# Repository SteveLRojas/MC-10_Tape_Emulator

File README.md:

# MC-10_Tape_Emulator
Unified HW and SW repository for the TRS-80 MC-10 tape emulator project.

## Dev Plan (USB Lib/FATFS)
✅- Get the STM to compile, 
- investigate funcs on top of in/out/transact to see how to use them to accomplish various operations
- Try to enumerate?
- Build bulk-only stuff?
- Implement SCSI stuff using bulk-only?
- ...??
- Glue functions?

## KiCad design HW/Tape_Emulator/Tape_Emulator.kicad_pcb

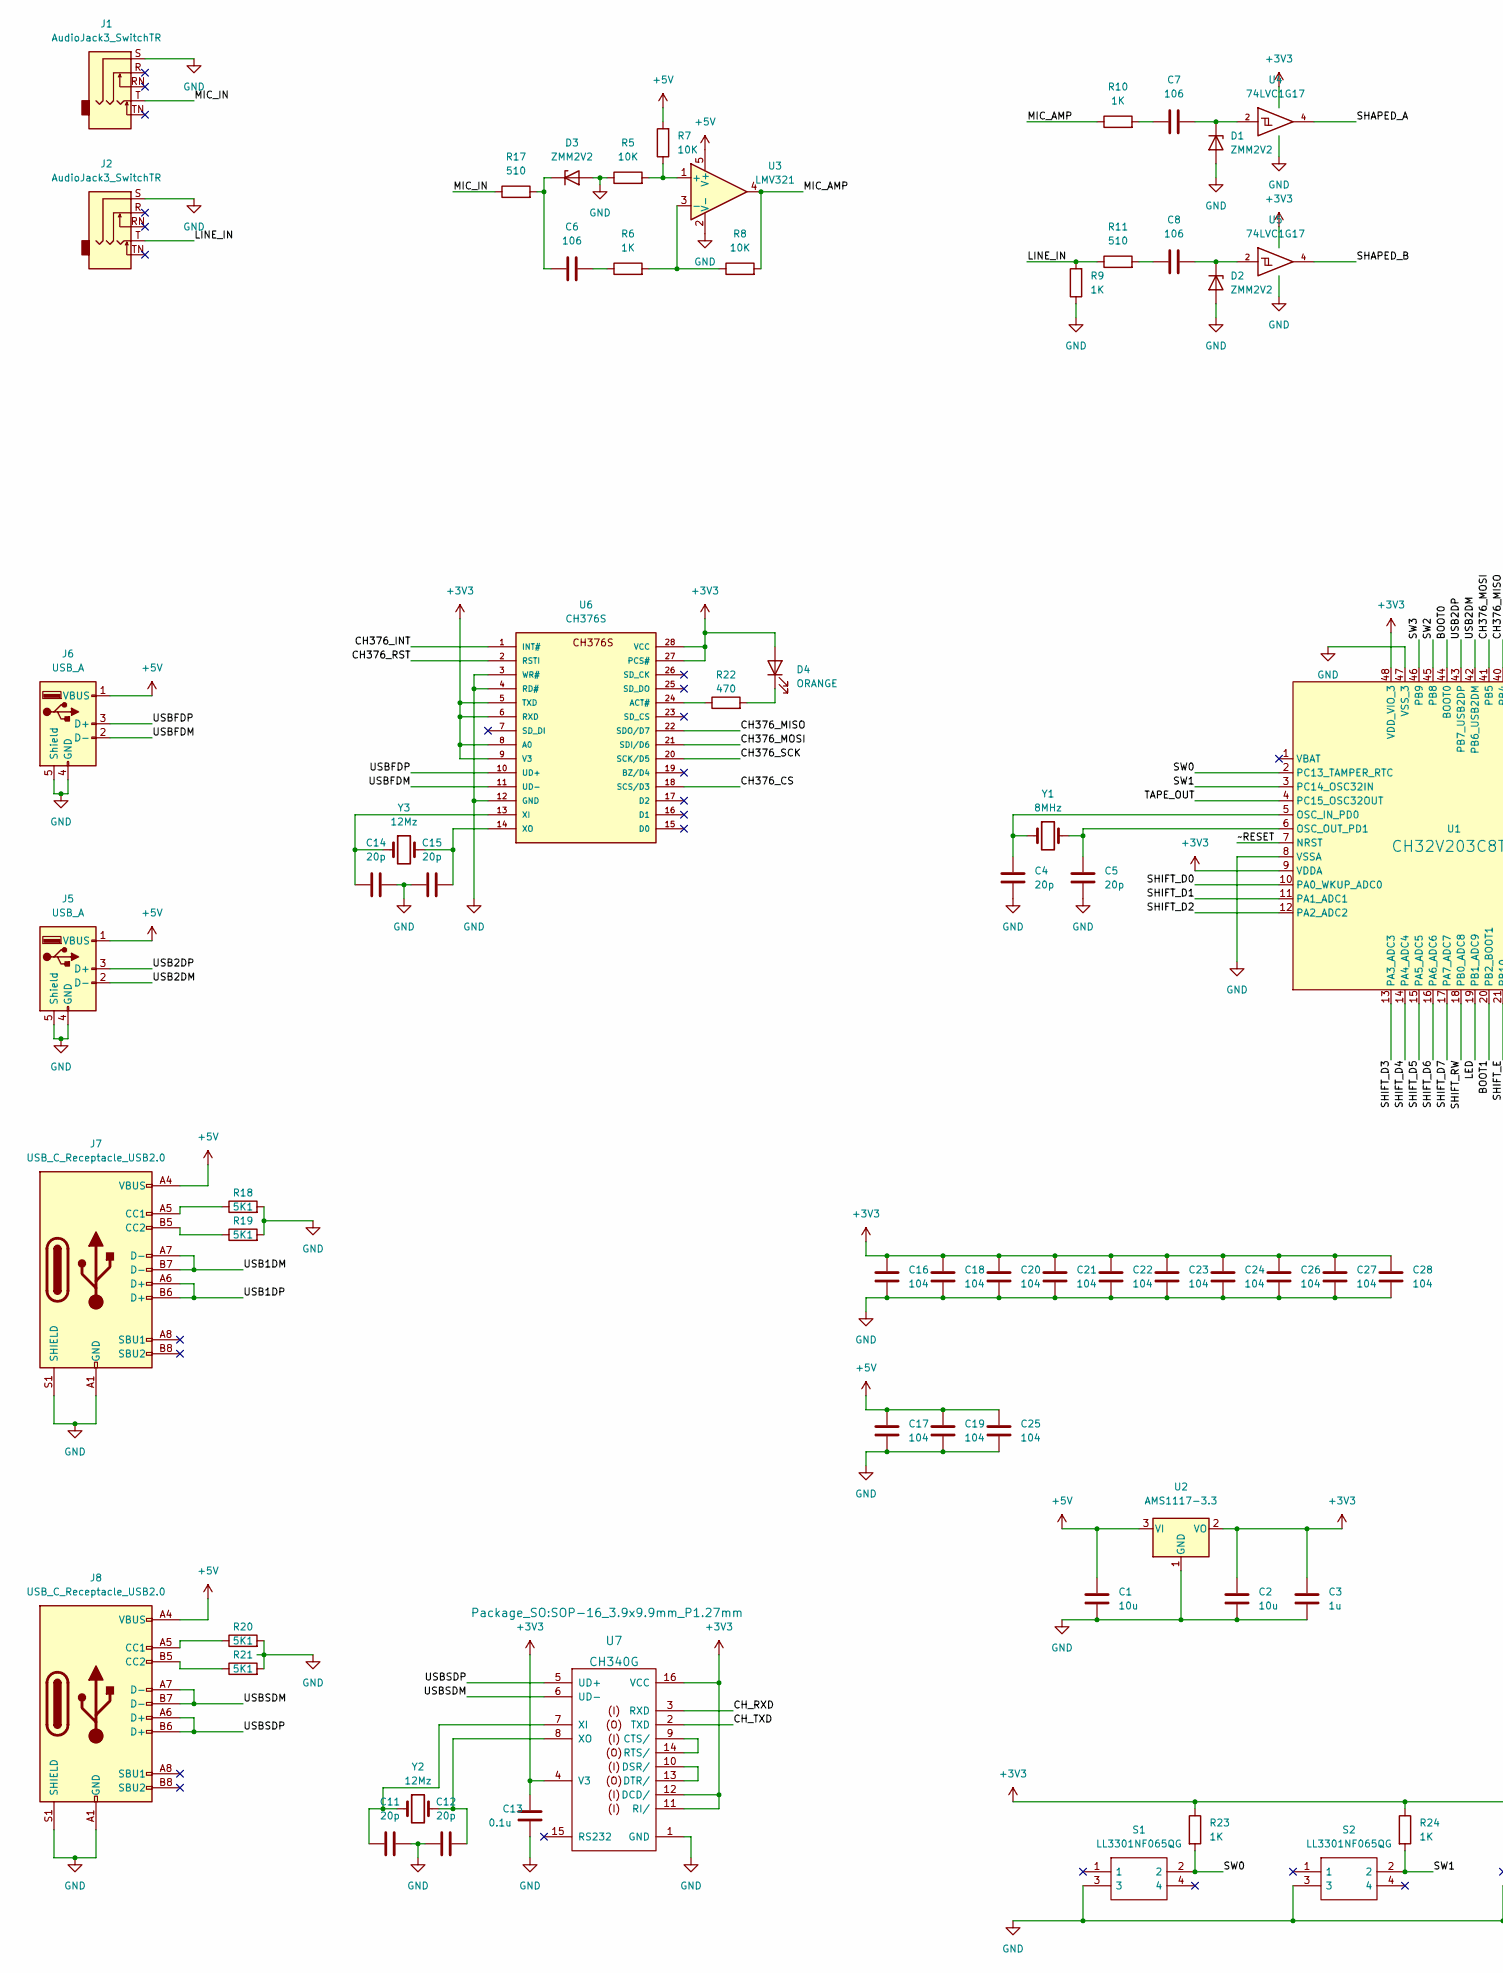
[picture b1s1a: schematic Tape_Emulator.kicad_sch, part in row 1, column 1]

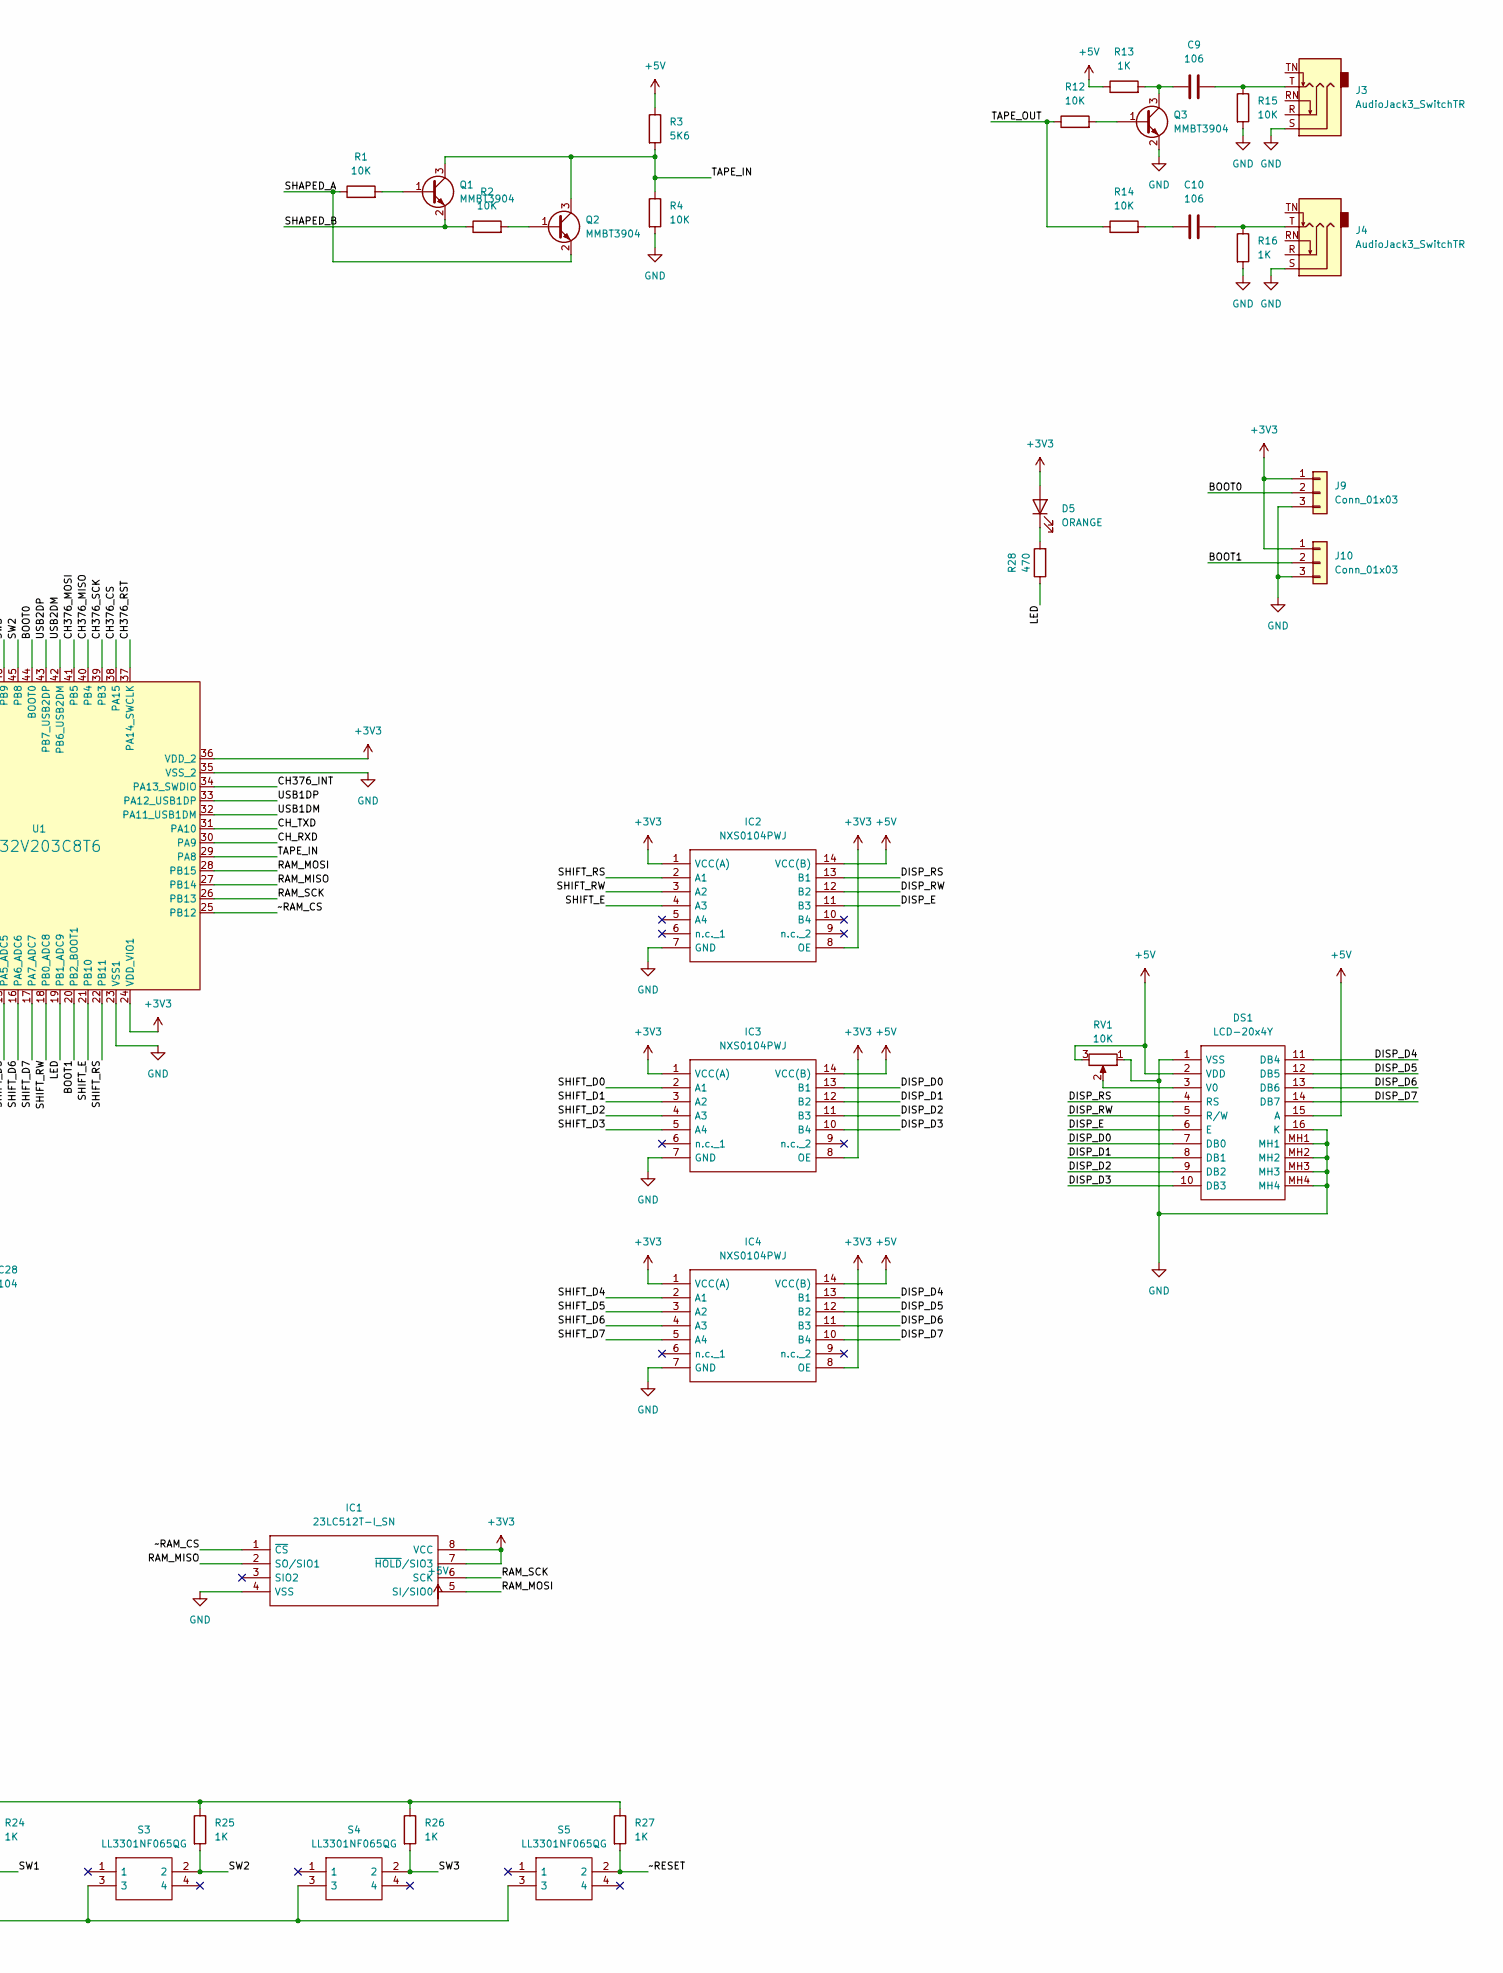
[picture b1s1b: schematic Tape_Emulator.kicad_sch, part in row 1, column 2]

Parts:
C1, C2: 10u; C_1206_3216Metric
C3: 1u; C_0805_2012Metric
C4, C5, C11, C12, C14, C15: 20p; C_0805_2012Metric
C6, C7, C8, C9, C10: 106; C_1206_3216Metric
C13: 0.1u; C_0805_2012Metric
C16, C17, C18, C19, C20, C21, C22, C23, C24, C25, C26, C27, C28: 104; C_0805_2012Metric
D1, D2, D3: ZMM2V2; D_MiniMELF
D4, D5: ORANGE; LED_0805_2012Metric
DS1: LCD-20x4Y; LCD20x4Y; Mouser Part Number 992-LCD-20X4Y
IC1: 23LC512T-I_SN; SOIC127P600X175-8N; Mouser Part Number 579-23LC512T-I/SN
IC2, IC3, IC4: NXS0104PWJ; SOP65P640X110-14N; Mouser Part Number 771-NXS0104PWJ
J1, J2, J3, J4: AudioJack3_SwitchTR; Jack_3.5mm_CUI_SJ1-3525N_Horizontal
J5, J6: USB_A; USB_A_CONNFLY_DS1095-WNR0
J7, J8: USB_C_Receptacle_USB2.0; USB_C_Receptacle_HRO_TYPE-C-31-M-12
J9, J10: Conn_01x03; PinHeader_1x03_P2.54mm_Vertical
Q1, Q2, Q3: MMBT3904; SOT-23
R1, R2, R4, R5, R7, R8, R12, R14, R15: 10K; R_0805_2012Metric
R3: 5K6; R_0805_2012Metric
R6, R9, R10, R13, R16, R23, R24, R25, R26, R27: 1K; R_0805_2012Metric
R11, R17: 510; R_0805_2012Metric
R18, R19, R20, R21: 5K1; R_0805_2012Metric
R22, R28: 470; R_0805_2012Metric
RV1: 10K; Potentiometer_Runtron_RM-065_Vertical
S1, S2, S3, S4, S5: LL3301NF065QG; Mouser Part Number 612-LL3301NF065QG
U1: CH32V203C8T6; CH32V203C8T6_LQFP-48_7x7mm_P0.5mm
U2: AMS1117-3.3; SOT-223-3_TabPin2
U3: LMV321; SOT-23-5
U4, U5: 74LVC1G17; SOT-23-5
U6: CH376S; SOP28
U7: CH340G; SOP-16_3.9x9.9mm_P1.27mm
Y1: 8MHz; Crystal_HC49-4H_Vertical
Y2, Y3: 12Mz; Crystal_HC49-U_Vertical

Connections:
+3V3: C2.1, C3.1, C13.1, C16.1, C18.1, C20.1, C21.1, C22.1, C23.1, C24.1, C26.1, C27.1, C28.1, D4.2 (A), D5.2 (A), IC1.7 (~HOLD/SIO3), IC1.8 (VCC), IC2.1 (VCC(A)), IC2.8 (OE), IC3.1 (VCC(A)), IC3.8 (OE), IC4.1 (VCC(A)), IC4.8 (OE), J9.1, J10.1, R23.1, R24.1, R25.1, R26.1, R27.1, U1.9 (VDDA), U1.24 (VDD_VIO1), U1.36 (VDD_2), U1.48 (VDD_VIO_3), U2.2 (VO), U4.5 (VCC), U5.5 (VCC), U6.5 (TXD), U6.6 (RXD), U6.8 (A0), U6.9 (V3), U6.27 (PCS#), U6.28 (VCC), U7.4 (V3), U7.11 (RI/), U7.12 (DCD/), U7.16 (VCC)
+5V: C1.1, C17.1, C19.1, C25.1, DS1.2 (VDD), DS1.15 (A), IC2.14 (VCC(B)), IC3.14 (VCC(B)), IC4.14 (VCC(B)), J5.1 (VBUS), J6.1 (VBUS), J7.A4 (VBUS), J7.A9 (VBUS), J7.B4 (VBUS), J7.B9 (VBUS), J8.A4 (VBUS), J8.A9 (VBUS), J8.B4 (VBUS), J8.B9 (VBUS), R3.1, R7.2, R13.1, RV1.3, U2.3 (VI), U3.5 (V+)
/BOOT0: J9.2, U1.44 (BOOT0)
/BOOT1: J10.2, U1.20 (PB2_BOOT1)
/CH376_CS: U1.38 (PA15), U6.18 (SCS/D3)
/CH376_INT: U1.34 (PA13_SWDIO), U6.1 (INT#)
/CH376_MISO: U1.40 (PB4), U6.22 (SDO/D7)
/CH376_MOSI: U1.41 (PB5), U6.21 (SDI/D6)
/CH376_RST: U1.37 (PA14_SWCLK), U6.2 (RSTI)
/CH376_SCK: U1.39 (PB3), U6.20 (SCK/D5)
/CH_RXD: U1.30 (PA9), U7.3 (RXD)
/CH_TXD: U1.31 (PA10), U7.2 (TXD)
/DISP_D0: DS1.7 (DB0), IC3.13 (B1)
/DISP_D1: DS1.8 (DB1), IC3.12 (B2)
/DISP_D2: DS1.9 (DB2), IC3.11 (B3)
/DISP_D3: DS1.10 (DB3), IC3.10 (B4)
/DISP_D4: DS1.11 (DB4), IC4.13 (B1)
/DISP_D5: DS1.12 (DB5), IC4.12 (B2)
/DISP_D6: DS1.13 (DB6), IC4.11 (B3)
/DISP_D7: DS1.14 (DB7), IC4.10 (B4)
/DISP_E: DS1.6 (E), IC2.11 (B3)
/DISP_RS: DS1.4 (RS), IC2.13 (B1)
/DISP_RW: DS1.5 (R/W), IC2.12 (B2)
/LED: R28.1, U1.19 (PB1_ADC9)
/LINE_IN: J2.T, R9.2, R11.1
/MIC_AMP: R8.2, R10.1, U3.4
/MIC_IN: J1.T, R17.1
/RAM_MISO: IC1.2 (SO/SIO1), U1.27 (PB14)
/RAM_MOSI: IC1.5 (SI/SIO0), U1.28 (PB15)
/RAM_SCK: IC1.6 (SCK), U1.26 (PB13)
/SHAPED_A: Q2.2 (E), R1.1, U4.4
/SHAPED_B: Q1.2 (E), R2.1, U5.4
/SHIFT_D0: IC3.2 (A1), U1.10 (PA0_WKUP_ADC0)
/SHIFT_D1: IC3.3 (A2), U1.11 (PA1_ADC1)
/SHIFT_D2: IC3.4 (A3), U1.12 (PA2_ADC2)
/SHIFT_D3: IC3.5 (A4), U1.13 (PA3_ADC3)
/SHIFT_D4: IC4.2 (A1), U1.14 (PA4_ADC4)
/SHIFT_D5: IC4.3 (A2), U1.15 (PA5_ADC5)
/SHIFT_D6: IC4.4 (A3), U1.16 (PA6_ADC6)
/SHIFT_D7: IC4.5 (A4), U1.17 (PA7_ADC7)
/SHIFT_E: IC2.4 (A3), U1.21 (PB10)
/SHIFT_RS: IC2.2 (A1), U1.22 (PB11)
/SHIFT_RW: IC2.3 (A2), U1.18 (PB0_ADC8)
/SW0: R23.2, S1.2, U1.2 (PC13_TAMPER_RTC)
/SW1: R24.2, S2.2, U1.3 (PC14_OSC32IN)
/SW2: R25.2, S3.2, U1.45 (PB8)
/SW3: R26.2, S4.2, U1.46 (PB9)
/TAPE_IN: Q1.3 (C), Q2.3 (C), R3.2, R4.1, U1.29 (PA8)
/TAPE_OUT: R12.1, R14.1, U1.4 (PC15_OSC32OUT)
/USB1DM: J7.A7 (D-), J7.B7 (D-), U1.32 (PA11_USB1DM)
/USB1DP: J7.A6 (D+), J7.B6 (D+), U1.33 (PA12_USB1DP)
/USB2DM: J5.2 (D-), U1.42 (PB6_USB2DM)
/USB2DP: J5.3 (D+), U1.43 (PB7_USB2DP)
/USBFDM: J6.2 (D-), U6.11 (UD-)
/USBFDP: J6.3 (D+), U6.10 (UD+)
/USBSDM: J8.A7 (D-), J8.B7 (D-), U7.6 (UD-)
/USBSDP: J8.A6 (D+), J8.B6 (D+), U7.5 (UD+)
/~RAM_CS: IC1.1 (~CS), U1.25 (PB12)
/~RESET: R27.2, S5.2, U1.7 (NRST)
GND: C1.2, C2.2, C3.2, C4.2, C5.2, C11.2, C12.1, C13.2, C14.2, C15.1, C16.2, C17.2, C18.2, C19.2, C20.2, C21.2, C22.2, C23.2, C24.2, C25.2, C26.2, C27.2, C28.2, D1.2 (A), D2.2 (A), D3.2 (A), DS1.1 (VSS), DS1.16 (K), DS1.MH1, DS1.MH2, DS1.MH3, DS1.MH4, IC1.4 (VSS), IC2.7 (GND), IC3.7 (GND), IC4.7 (GND), J1.S, J2.S, J3.S, J4.S, J5.4 (GND), J5.5 (Shield), J6.4 (GND), J6.5 (Shield), J7.A1 (GND), J7.A12 (GND), J7.B1 (GND), J7.B12 (GND), J7.S1 (SHIELD), J8.A1 (GND), J8.A12 (GND), J8.B1 (GND), J8.B12 (GND), J8.S1 (SHIELD), J9.3, J10.3, Q3.2 (E), R4.2, R5.1, R9.1, R15.2, R16.2, R18.2, R19.2, R20.2, R21.2, RV1.1, S1.3, S2.3, S3.3, S4.3, S5.3, U1.8 (VSSA), U1.23 (VSS1), U1.35 (VSS_2), U1.47 (VSS_3), U2.1 (GND), U3.2 (V-), U4.3 (GND), U5.3 (GND), U6.3 (WR#), U6.4 (RD#), U6.12 (GND), U7.1 (GND)
unnamed: C4.1, U1.5 (OSC_IN_PD0), Y1.1
unnamed: C5.1, U1.6 (OSC_OUT_PD1), Y1.2
unnamed: C6.1, D3.1 (K), R17.2
unnamed: C6.2, R6.1
unnamed: C7.1, R10.2
unnamed: C7.2, D1.1 (K), U4.2
unnamed: C8.1, R11.2
unnamed: C8.2, D2.1 (K), U5.2
unnamed: C9.1, Q3.3 (C), R13.2
unnamed: C9.2, J3.T, R15.1
unnamed: C10.1, R14.2
unnamed: C10.2, J4.T, R16.1
unnamed: C11.1, U7.7 (XI), Y2.1
unnamed: C12.2, U7.8 (XO), Y2.2
unnamed: C14.1, U6.13 (XI), Y3.1
unnamed: C15.2, U6.14 (XO), Y3.2
unnamed: D4.1 (K), R22.2
unnamed: D5.1 (K), R28.2
unnamed: DS1.3 (V0), RV1.2
unnamed: J7.A5 (CC1), R18.1
unnamed: J7.B5 (CC2), R19.1
unnamed: J8.A5 (CC1), R20.1
unnamed: J8.B5 (CC2), R21.1
unnamed: Q1.1 (B), R1.2
unnamed: Q2.1 (B), R2.2
unnamed: Q3.1 (B), R12.2
unnamed: R5.2, R7.1, U3.1 (+)
unnamed: R6.2, R8.1, U3.3 (-)
unnamed: R22.1, U6.24 (ACT#)
unnamed: U7.10 (DSR/), U7.13 (DTR/)
unnamed: U7.9 (CTS/), U7.14 (RTS/)

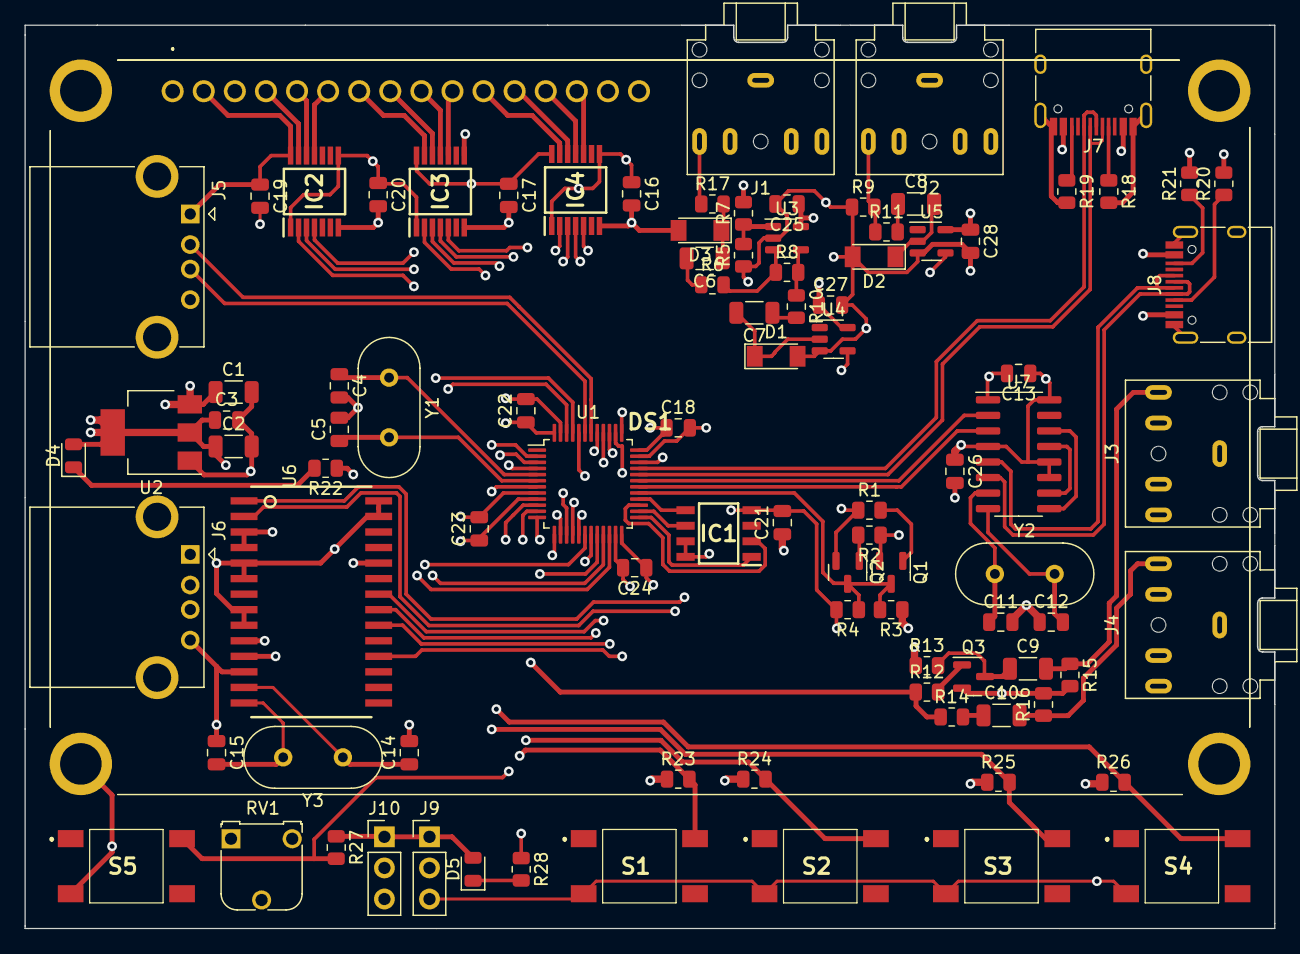
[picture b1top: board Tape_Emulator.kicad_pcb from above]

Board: 4 copper layers, 102.1 x 73.8 mm, 95 parts (0 on the bottom side), 91 nets.

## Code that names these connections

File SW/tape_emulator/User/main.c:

#include "ch32v20x.h"
#include "fifo.h"
#include "ch32v203_afio.h"
#include "ch32v203_core.h"
#include "ch32v203_gpio.h"
#include "ch32v203_rcc.h"
//#include "ch32v203_spi.h"
//#include "ch32v203_timer.h"
#include "ch32v203_uart.h"
//#include "ch32v203_usbd.h"
#include "ch32v203_usbd_cdc.h"
//#include "ch32v203_usbfsd.h"
#include "ch32v203_usbfsh.h"
//#include "pseudo_random.h"
#include "debug.h"
#include "support.h"
#include "lcd.h"
#include "usbfsh_msc_bot.h"

//Pins:
// DISP = PA0 - PA7
// TAPE_IN = PA8
// CH_RXD = PA9
// CH_TXD = PA10
// USB1DM = PA11
// USB1DP = PA12
// CH376_INT = PA13
// CH376_RST = PA14
// CH376_CS = PA15
// DISP_RW = PB0
// LED = PB1
// BOOT1 = PB2
// CH376_SCK = PB3
// CH376_MISO = PB4
// CH376_MOSI = PB5
// USB2DM = PB6
// USB2DP = PB7
// SW2 = PB8
// SW3 = PB9
// DISP_E = PB10
// DISP_RS = PB11
// RAM_CS = PB12
// RAM_SCK = PB13
// RAM_MISO = PB14
// RAM_MOSI = PB15
// SW0 = PC13
// SW1 = PC14
// TAPE_OUT = PC15

void print_bytes_as_hex(const uint8_t* source, uint8_t num_bytes)
{
	uint8_t idx;

	for(idx = 0; idx < num_bytes; ++idx)
	{
		printf("%02X: %02X\n", idx, source[idx]);
	}
}

int main(void)
{
	rcc_apb2_clk_enable(RCC_AFIOEN | RCC_IOPAEN | RCC_IOPBEN | RCC_IOPCEN | RCC_TIM1EN | RCC_SPI1EN | RCC_USART1EN);
	rcc_apb1_clk_enable(RCC_TIM2EN | RCC_USBEN);
	rcc_ahb_clk_enable(RCC_USBFS);

	gpio_set_mode(GPIOA, GPIO_DIR_SPD_OUT_50MHZ | GPIO_MODE_PP_OUT, GPIO_PIN_0 | GPIO_PIN_1 | GPIO_PIN_2 | GPIO_PIN_3 | GPIO_PIN_4 | GPIO_PIN_5 | GPIO_PIN_6 | GPIO_PIN_7 | GPIO_PIN_14 | GPIO_PIN_15);
	gpio_set_mode(GPIOA, GPIO_DIR_SPD_IN | GPIO_MODE_FLOAT_IN, GPIO_PIN_8 | GPIO_PIN_10 | GPIO_PIN_13);
	gpio_set_mode(GPIOA, GPIO_DIR_SPD_OUT_50MHZ | GPIO_MODE_AFIO_PP, GPIO_PIN_9);

	gpio_set_mode(GPIOB, GPIO_DIR_SPD_OUT_50MHZ | GPIO_MODE_PP_OUT, GPIO_PIN_0 | GPIO_PIN_1 | GPIO_PIN_10 | GPIO_PIN_11 | GPIO_PIN_12);
	gpio_set_mode(GPIOB, GPIO_DIR_SPD_IN | GPIO_MODE_FLOAT_IN, GPIO_PIN_8 | GPIO_PIN_9);

	gpio_set_mode(GPIOC, GPIO_DIR_SPD_IN | GPIO_MODE_FLOAT_IN, GPIO_PIN_13 | GPIO_PIN_14);
	gpio_set_mode(GPIOC, GPIO_DIR_SPD_OUT_2MHZ | GPIO_MODE_PP_OUT, GPIO_PIN_15);

	gpio_set_pin(GPIOA, GPIO_PIN_14);
	gpio_set_pin(GPIOB, GPIO_PIN_12);

	Delay_Init();
	uart_init(USART1, 115200);
	core_enable_irq(USART1_IRQn);

	printf("SYSCLK: %u\n", rcc_compute_sysclk_freq());
	printf("HCLK: %u\n", rcc_compute_hclk_freq());
	printf("PCLK1: %u\n", rcc_compute_pclk1_freq());
	printf("PCLK2: %u\n", rcc_compute_pclk2_freq());
	printf("ADCCLK: %u\n", rcc_compute_adcclk());

	// blink the led once
	gpio_clear_pin(GPIOB, GPIO_PIN_1);
	Delay_Ms(100);
	gpio_set_pin(GPIOB, GPIO_PIN_1);
	printf("Unicorn\n");

	cdc_init();
	cdc_set_serial_state(0x03);

	lcd_init();
	lcd_print_string("Tape Emulator");

	usbfsh_msc_bot_init();

	uint8_t button_state_prev[4];
	uint8_t connected_state_prev;
	button_state_prev[0] = gpio_read_pin(GPIOC, GPIO_PIN_13);
	button_state_prev[1] = gpio_read_pin(GPIOC, GPIO_PIN_14);
	button_state_prev[2] = gpio_read_pin(GPIOB, GPIO_PIN_8);
	button_state_prev[3] = gpio_read_pin(GPIOB, GPIO_PIN_9);
	connected_state_prev = usbfsh_port_is_attached();
	while(1)
	{
		if(!gpio_read_pin(GPIOC, GPIO_PIN_13) && button_state_prev[0])
		{
			printf("S1 Pressed\n");
			if(usbfsh_msc_bot_configure())
				printf("Configuration successful\n");
			else
				printf("Configuration failed\n");
		}
		if(!gpio_read_pin(GPIOC, GPIO_PIN_14) && button_state_prev[1])
			printf("S2 Pressed\n");
		if(!gpio_read_pin(GPIOB, GPIO_PIN_8) && button_state_prev[2])
			printf("S3 Pressed\n");
		if(!gpio_read_pin(GPIOB, GPIO_PIN_9) && button_state_prev[3])
			printf("S4 Pressed\n");

		if(usbfsh_port_is_attached() & ~connected_state_prev)
			printf("Device connected\n");
		if(~usbfsh_port_is_attached() & connected_state_prev)
			printf("Device disconnected\n");

		button_state_prev[0] = gpio_read_pin(GPIOC, GPIO_PIN_13);
		button_state_prev[1] = gpio_read_pin(GPIOC, GPIO_PIN_14);
		button_state_prev[2] = gpio_read_pin(GPIOB, GPIO_PIN_8);
		button_state_prev[3] = gpio_read_pin(GPIOB, GPIO_PIN_9);
		connected_state_prev = usbfsh_port_is_attached();

		Delay_Ms(1);
	}
}

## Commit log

2023-05-27 Added files
2023-05-28 Enabled usb file read
2023-05-29 Fixed many bugs
2023-05-29 Write test data
2023-06-10 Write file
2023-10-27 Cleaned up project structure, added new HW
2023-11-26 Created MRS project
2023-12-19 Did some stuff
2024-01-12 removed backups
2024-01-13 added CDC test project
2024-01-13 Added BOM
2024-01-14 Created CDC FIFO in test project
2024-01-14 Cleaned up CDC test project
2024-01-21 CDC now using fifo buffers, cleanup pending
2024-01-25 implemented fifo to pma copy function
2024-01-27 Implemented PMA to receive buffer copy function
2024-01-27 Cleaned up code
2024-01-27 cleanup stuff
2024-02-10 Created CDC interface files
2024-02-10 removed/replaced stuff from UART.c UART.h
2024-02-10 Completed CDC serial, needs checking/cleanup
2024-02-18 Completed CDC test project
2024-03-07 Added USB mass storage test projects
2024-03-12 WIP implementing SCSI and BOT
2024-03-17 Got SCSI TestUnitReady partially working
2024-03-27 Using LED and buttons, SCSI TestUnitReady working for most flash drives
2024-03-31 Got SCSI Inquiry working, improved enumeration
2024-04-01 Got SCSI ReadCapacity working
2024-05-04 Get endpoint number from endpoint descriptor
2024-05-08 Got SCSI read working
2024-05-25 FatFs glue functions, got file read working
2024-05-26 Got file write working
2024-09-04 Created a new MRS project without WCH libraries
2024-09-07 Enumerate and configure flash drive using new libraries
2025-04-16 mystery changes I forgot to commit...
